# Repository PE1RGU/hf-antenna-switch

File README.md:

# HF Antenna Switch

**A remote antenna switch for an HF amateur radio station: 3 radios, 4 antennas, one Cat6 cable, and the safety rules in hardware.**
**Designed by a radio amateur together with an AI assistant, and documented decision by decision.**

<p align="center"><em>Left: the outdoor unit, lid removed. Right: the shack interface, cover removed. CAD views of the current design, not photos.</em></p>

The relay unit sits outdoors, close to the antennas, in a milled aluminium case.
A small interface box in the shack controls it over one Cat6 cable.
A computer sends the commands over USB.
If anything goes wrong (a cable break, a box fault, a press on the KILL switch), every radio is inhibited and every relay is released, without help from the firmware.

> **Status: design phase.** Schematics, layouts and the case are drawn and checked by scripts. No board is built yet, and nothing here is tested on the bench. The shack interface firmware runs in an emulator on the computer.

## In numbers

| | |
|---|---|
| Radios | 3, each with its own transmit antenna and receive antenna |
| Antennas | 4 per unit; a second unit adds 4 more |
| Frequency range | 1.8 to 54 MHz |
| Power | 100 W, SWR up to 3:1 |
| Relays | 37 × TE RT1, one type everywhere |
| RF board | 6 layers, 50 Ω coplanar lines |
| Link to the shack | One Cat6 cable, four opto-isolated current loops |
| Outdoor case | Milled aluminium tray, 288 × 250 × 66 mm |
| Shack case | Hammond 1455T1601 extrusion, PCB end plates |
| Controllers | ESP32-C3 in the box and in the shack |

## Why this project may interest you

**Safety in hardware, not only in software.**
A receive-only antenna (such as a loop with a preamplifier) never sees transmit power.
No relay switches while RF is present.
The firmware may ask for a state. The hardware decides whether that state is allowed.

**Designed with an AI, in the open.**
This is an experiment in how a person and an AI assistant (Claude, by Anthropic) design hardware together.
I set the goals and took the decisions. The AI did much of the research, the calculations and the scripts.
The [design log](design-log.md) records every decision, who took it, and why. Rejected options stay in it too.
See [docs/how-this-was-made.md](docs/how-this-was-made.md) for the method and its limits.

**Everything comes from scripts.**
Schematics, footprints, board placement, routing, end plates, the 3D fit checks and these renders are all generated by Python scripts.
A change is repeatable, and two revisions can be compared.
The logic is checked with truth tables against the real netlists.
[tools/README.md](tools/README.md) lists every script and how to run it.

## What it does

- Connects each of 3 radios to a transmit antenna and, separately, to a receive antenna.
- Keeps receive-only antennas away from transmit power.
- Changes relays only when no RF is present (TX inhibit and handshake per radio).
- Stops all transmission and releases all relays on any fault, cable break or KILL switch.
- Grounds antennas that are not in use, through a static bleed.
- Feeds an active receive antenna through a switched bias-T.
- Is controlled from a computer over USB through the shack interface.

## System overview

```mermaid
flowchart LR
  subgraph SHACK["Shack"]
    PC["Computer"]
    SI["Shack interface<br/>SAFE latch, TX permits,<br/>radio ports R1 to R3"]
    R1["R1 FT-710"]
    R2["R2"]
    R3["R3"]
  end
  subgraph BOX["Outdoor unit, milled aluminium case"]
    CB["Controller board<br/>ESP32-C3, safety gate, watchdog"]
    RF["RF board<br/>3 radios x 4 antennas<br/>37 x TE RT1 relays"]
  end
  subgraph ANT["Antennas"]
    A1["A1 G5RV"]
    A2["A2 RX loop"]
    A34["A3, A4 spare"]
  end
  U2["Unit 2, optional<br/>+4 antennas"]
  PC -- USB --> SI
  SI == "Cat6: 4 opto current loops" ==> CB
  CB -- I2C --> RF
  R1 -- coax --> RF
  R2 -- coax --> RF
  R3 -- coax --> RF
  R1 -.- SI
  R2 -.- SI
  R3 -.- SI
  RF --> A1
  RF --> A2
  RF --> A34
  RF -. "EXP: SMA + ribbon" .-> U2
```

The dotted lines from the radios are the TUNER and LINEAR jacks (TX inhibit, PTT sense).
More detail, and the reason for each choice, is in [docs/architecture.md](docs/architecture.md).

## The outdoor unit

The RF board carries the relay matrix: per radio a changeover relay, a transmit row and a receive row; per antenna a ground relay, a static bleed, an RF detector and an optional bias-T.
The controller board sits on standoffs above it.

<p align="center"><em>Controller board (KiCad render). Left: the Cat6 link with the opto current loops and a 3 mm isolation gap. Right: the ESP32-C3 DevKit. The NOR gate on the silkscreen is the relay enable: RLY_EN = NOR(KILL, MCU_EN_N, FAULT).</em></p>

## The shack interface

The shack interface powers the four current loops, holds the SAFE latch and the transmit permits, and connects to the three radios.
At the front: a 2 inch colour display, the SAFE and LATCHED LEDs, RESET and the KILL switch.
At the rear: 13.8 V DC, Cat6 to the outdoor unit, USB and the three radio ports.

<p align="center"><em>Front and rear of the shack interface (SolidCraft views).</em></p>

## Safety chain

The SAFE loop is one series current loop from the shack to the box and back.
Any break stops the current: KILL switch, cable cut, box fault, or loss of power.
All radios are then inhibited and all relays released, in hardware, without help from the firmware.

Radios R2 and R3 transmit only after a handshake with the box: request, state check, relay set, read-back, permit.

All logic, timing and flow diagrams:

| Diagram | Content |
|---|---|
| [L1](hardware/docs/diagrams/L1_safe_loop.svg) | SAFE loop |
| [L2](hardware/docs/diagrams/L2_box_safety_gate.svg) | Box safety gate |
| [L3](hardware/docs/diagrams/L3_shack_latch_port.svg) | Shack latch and radio port |
| [T1](hardware/docs/diagrams/T1_box_startup.svg) | Box start-up timing |
| [T2](hardware/docs/diagrams/T2_safe_stop.svg) | SAFE stop timing |
| [T3a](hardware/docs/diagrams/T3a_tx_start.svg), [T3b](hardware/docs/diagrams/T3b_tx_end.svg) | TX start and TX end timing |
| [T4](hardware/docs/diagrams/T4_ptt_r1.svg) | R1 PTT loop timing |
| [F1](hardware/docs/diagrams/F1_box_firmware.svg) | Box firmware flow |
| [F2](hardware/docs/diagrams/F2_tx_handshake.svg) | TX handshake for R2 and R3 |

## Firmware and emulator

The firmware is written in Rust and runs on an ESP32-C3 in the box and in the shack.
No board exists yet, so the firmware is developed in an emulator.
The emulator runs the same firmware logic that goes into the ESP32-C3, against models of the parts on the board: the I/O expander, the supervisors and latches, the SAFE loop, the radio ports, the data link to the box and the display.

<p align="center"><em>The emulated shack interface in a terminal. Left: pixel view, the 2 inch display exactly as the firmware draws it. Right: text view, for terminals without images. R1 transmits on A1 and receives on the loop A2; R2 uses A3.</em></p>

In the emulator you can:

- see the shack display as the firmware draws it (page B: radios, antennas and their routes; page C: one card per radio; the Safe stop screen with its cause and the steps to recover),
- press RESET and KILL, cut the cable, switch the supply, and let a radio transmit, with function keys,
- type the same commands that a station program sends over USB, or connect a program over TCP,
- stop it and start it again: the routes, names and page come back, as on the real unit; a transmission never does.

It runs in a terminal on macOS, Linux and Windows:

```bash
cd firmware
```

```bash
cargo run --release -p sim-shack
```

[firmware/README.md](firmware/README.md) explains how the emulator works, every key and command, and a first session step by step.
To read or change the code, start with the [firmware guide](firmware/docs/guide.md), written for hobby programmers.

## Where it stands

| Part | State |
|---|---|
| Requirements and architecture | Requirements in draft, architecture rev C |
| Schematics, all boards | Generated, ERC clean, logic checked by script |
| RF board layout | Placed and routed, DRC clean |
| Controller board layout | Placed and routed, DRC clean |
| Shack interface layout | Placed and routed, DRC clean; end plates drawn |
| Cases | Outdoor tray and shack end plates drawn; 3D fit checked |
| Firmware, shack interface | Runs in the emulator: permits, handshake, host protocol, display, stored settings; tested against the hardware logic |
| Firmware, box controller | Not started; a scripted box stands in for it in the emulator |
| Bench tests | Not started; see [docs/test/test-spec.md](docs/test/test-spec.md) |

The [CHANGELOG](CHANGELOG.md) has the details per revision.

## Documents

| Document | Content |
|---|---|
| [docs/requirements.md](docs/requirements.md) | What we build and what is important |
| [docs/architecture.md](docs/architecture.md) | System blocks, interfaces, main decisions |
| [docs/design/](docs/design/) | Detailed design, one document per board |
| [docs/test/test-spec.md](docs/test/test-spec.md) | How each requirement is tested |
| [design-log.md](design-log.md) | Every decision, assumption, calculation, standard and measurement, with its reason |
| [CHANGELOG.md](CHANGELOG.md) | Changes per revision |

## Repository layout

```
docs/                       requirements, architecture, design, test, images
hardware/unit/              outdoor unit: RF board, controller board, case, verification scripts
hardware/shack-interface/   shack interface board, end plates, case fit and renders
hardware/docs/diagrams/     logic, timing and flow diagrams
firmware/                   Rust firmware and the emulator (see firmware/README.md)
tools/README.md             where each generator and verification script is, and how to run it
Datasheets/                 datasheet register (the PDFs are not in the repository)
archive/                    earlier revisions (card cage and backplane, rev A/B)
```

## Tools

- KiCad 10, with the board layouts generated by Python scripts
- Rust for the firmware and the emulator (esp-hal, embedded-graphics, ratatui)
- Python 3 for the generators, the router and the verification scripts
- cadquery and SolidCraft for the cases, the 3D fit checks and the renders
- JLCPCB for the PCBs

## Licence

- Hardware design files and documentation: CERN Open Hardware Licence v2, Strongly Reciprocal (CERN-OHL-S-2.0). See [LICENSE](LICENSE).
- Python scripts (generators, verification) and the firmware (Rust): MIT. See [LICENSE-MIT](LICENSE-MIT).
- The display fonts compiled into the firmware are M+ FONTS (through the `mplusfonts` crate), under the SIL Open Font License 1.1.
- Vendor 3D models and libraries (SnapEDA, SamacSys, Ultra Librarian, Amass, Amphenol) are not in the repository. See [hardware/THIRD-PARTY.md](hardware/THIRD-PARTY.md) for where to get them.

Source Location (required by CERN-OHL-S): https://github.com/PE1RGU/hf-antenna-switch

73 de PE1RGU

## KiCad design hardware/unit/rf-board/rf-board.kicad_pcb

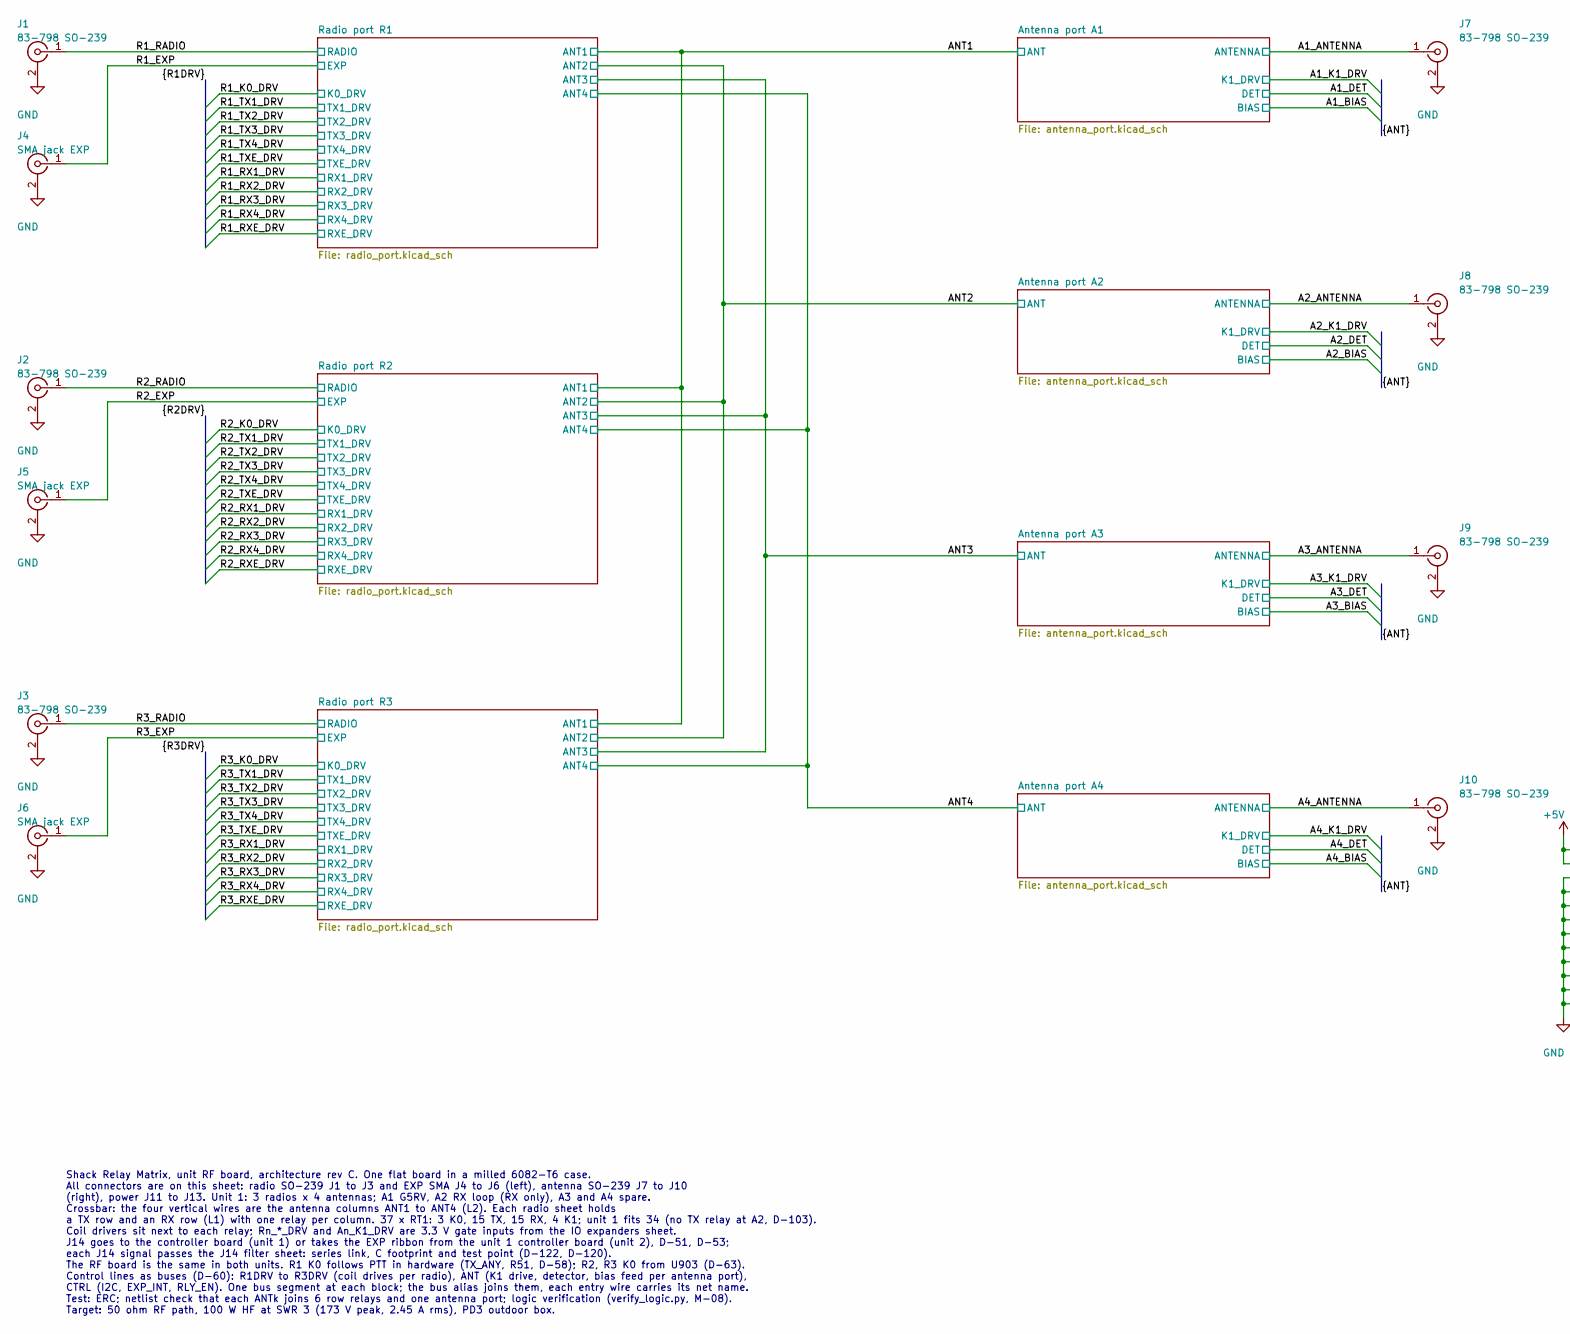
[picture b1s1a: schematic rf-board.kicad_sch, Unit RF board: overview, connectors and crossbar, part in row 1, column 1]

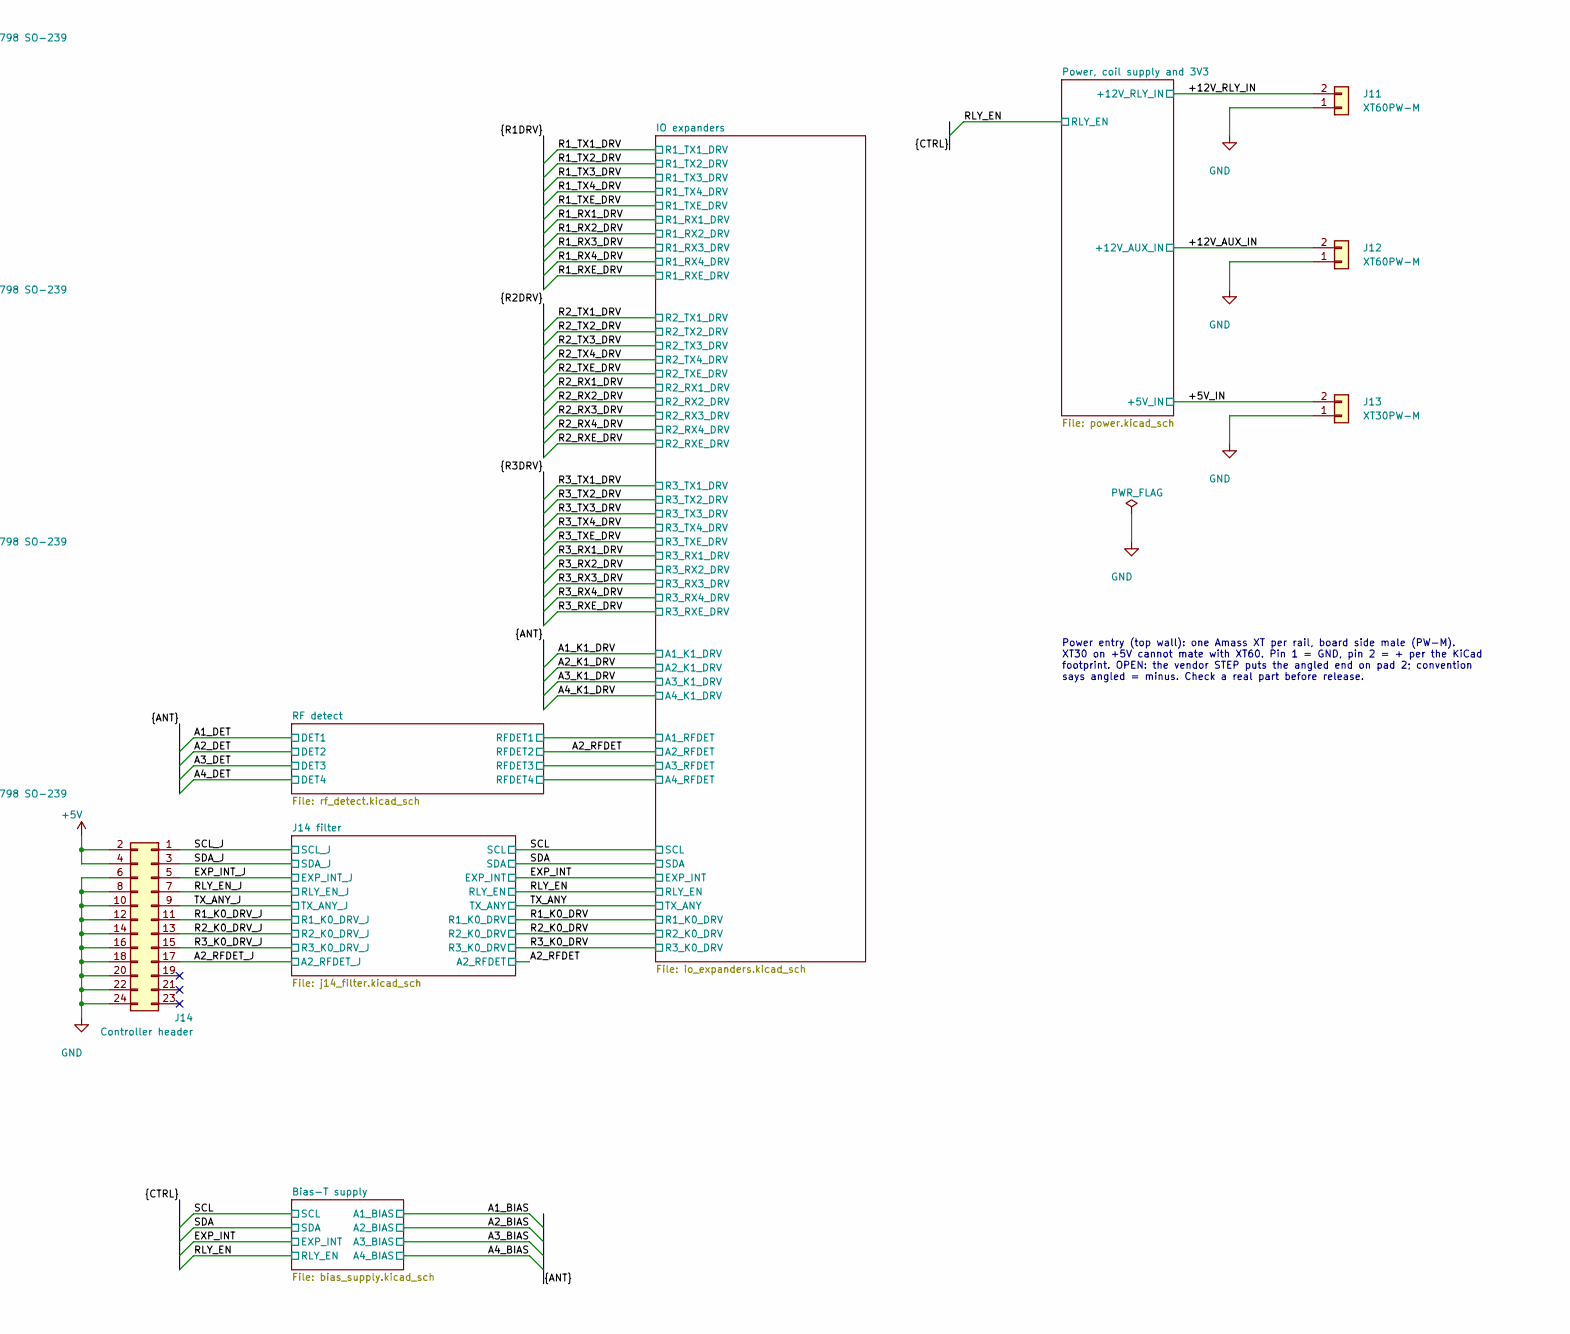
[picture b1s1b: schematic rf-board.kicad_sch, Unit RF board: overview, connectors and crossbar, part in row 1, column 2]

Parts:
J1, J2, J3, J7, J8, J9: 83-798 SO-239; SO239_83-798_StrapPad_BossRight; MPN 83-1R
J4, J5, J6: SMA jack EXP; SMA_901-9215_StrapPad; MPN 901-9215
J10: 83-798 SO-239; SO239_83-798_StrapPad_BossLeft; MPN 83-1R
J11, J12: XT60PW-M; AMASS_XT60PW-M_1x02_P7.20mm_Horizontal; MPN XT60PW-M
J13: XT30PW-M; AMASS_XT30PW-M_1x02_P2.50mm_Horizontal; MPN XT30PW-M
J14: Controller header; PinHeader_2x12_P2.54mm_Vertical; MPN TSW-112-07-L-D

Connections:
+5V: J14.2, J14.4; also elsewhere on the board
/+5V_IN: J13.2; also elsewhere on the board
/+12V_AUX_IN: J12.2; also elsewhere on the board
/+12V_RLY_IN: J11.2; also elsewhere on the board
/A1_ANTENNA: J7.1 (In); also elsewhere on the board
/A2_ANTENNA: J8.1 (In); also elsewhere on the board
/A2_RFDET_J: J14.17; also elsewhere on the board
/A3_ANTENNA: J9.1 (In); also elsewhere on the board
/A4_ANTENNA: J10.1 (In); also elsewhere on the board
/EXP_INT_J: J14.5; also elsewhere on the board
/R1_EXP: J4.1 (In); also elsewhere on the board
/R1_K0_DRV_J: J14.11; also elsewhere on the board
/R1_RADIO: J1.1 (In); also elsewhere on the board
/R2_EXP: J5.1 (In); also elsewhere on the board
/R2_K0_DRV_J: J14.13; also elsewhere on the board
/R2_RADIO: J2.1 (In); also elsewhere on the board
/R3_EXP: J6.1 (In); also elsewhere on the board
/R3_K0_DRV_J: J14.15; also elsewhere on the board
/R3_RADIO: J3.1 (In); also elsewhere on the board
/RLY_EN_J: J14.7; also elsewhere on the board
/SCL_J: J14.1; also elsewhere on the board
/SDA_J: J14.3; also elsewhere on the board
/TX_ANY_J: J14.9; also elsewhere on the board
GND: J1.2 (Ext), J2.2 (Ext), J3.2 (Ext), J4.2 (Ext), J5.2 (Ext), J6.2 (Ext), J7.2 (Ext), J8.2 (Ext), J9.2 (Ext), J10.2 (Ext), J11.1, J12.1, J13.1, J14.6, J14.8, J14.10, J14.12, J14.14, J14.16, J14.18, J14.20, J14.22, J14.24; also elsewhere on the board

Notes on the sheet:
Power entry (top wall): one Amass XT per rail, board side male (PW-M). XT30 on +5V cannot mate with XT60. Pin 1 = GND, pin 2 = + per the KiCad footprint. OPEN: the vendor STEP puts the angled end on pad 2; convention says angled = minus. Check a real part before release.
Shack Relay Matrix, unit RF board, architecture rev C. One flat board in a milled 6082-T6 case. All connectors are on this sheet: radio SO-239 J1 to J3 and EXP SMA J4 to J6 (left), antenna SO-239 J7 to J10 (right), power J11 to J13. Unit 1: 3 radios x 4 antennas; A1 G5RV, A2 RX loop (RX only), A3 a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

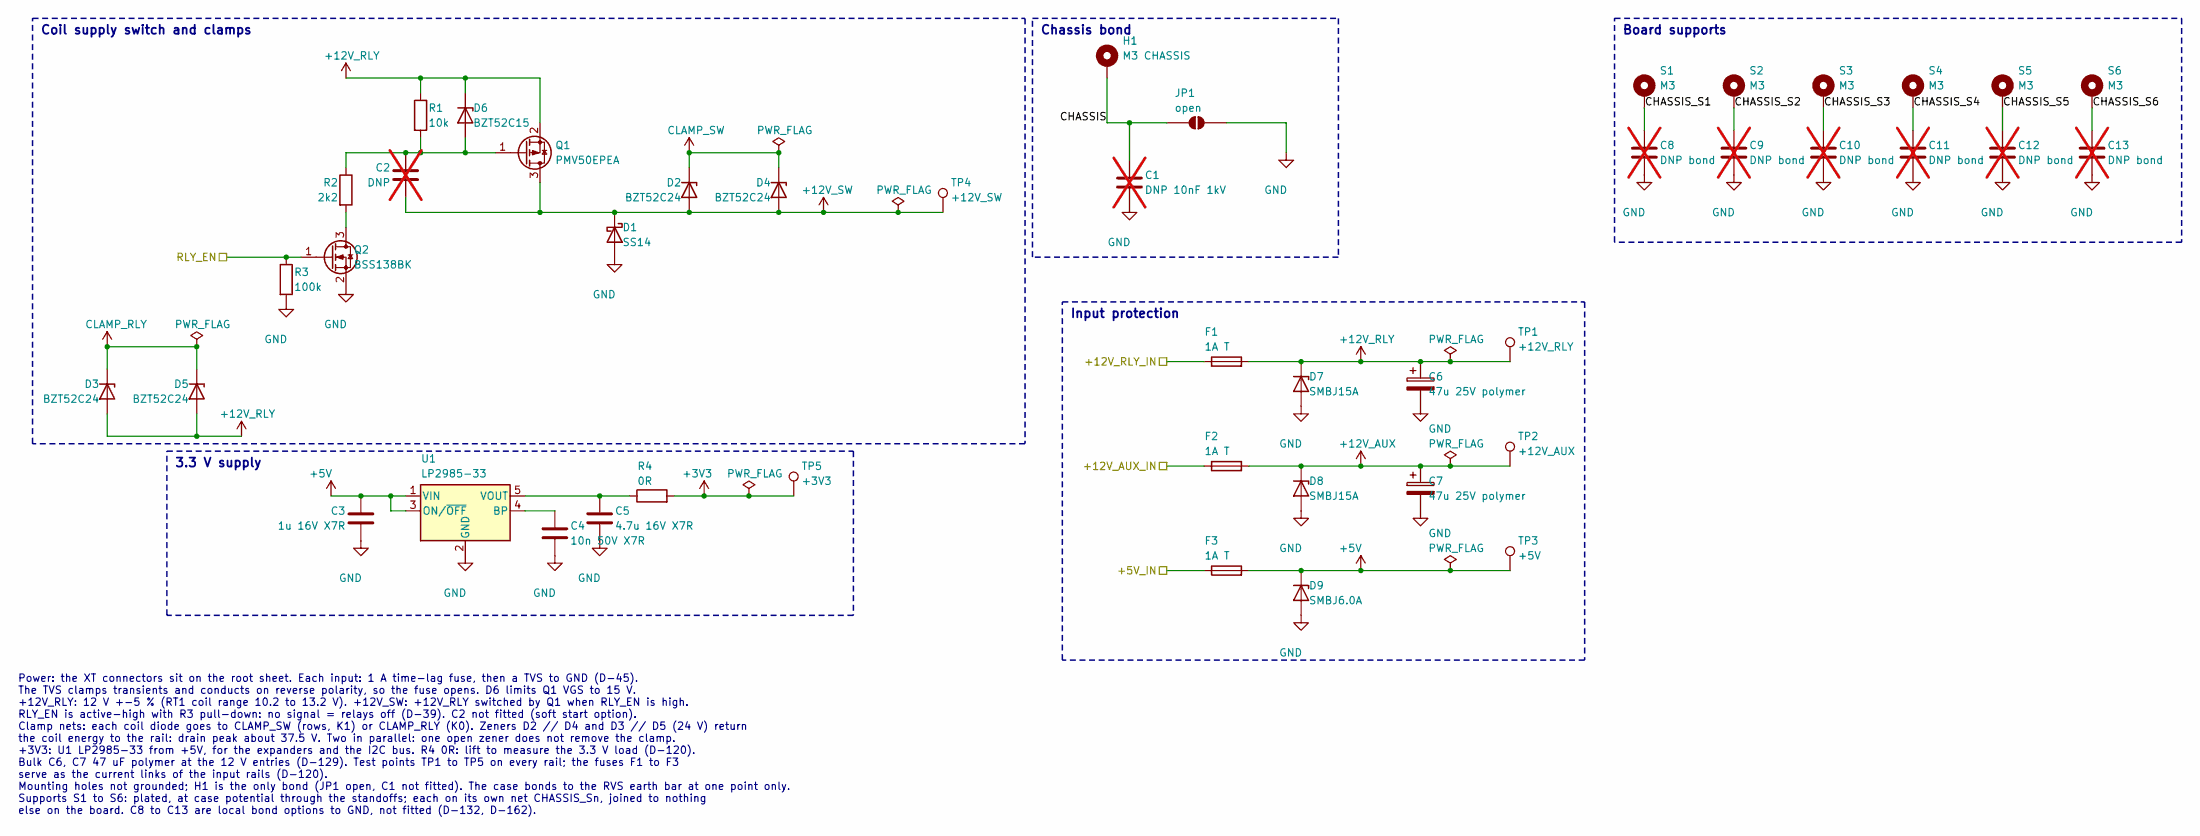
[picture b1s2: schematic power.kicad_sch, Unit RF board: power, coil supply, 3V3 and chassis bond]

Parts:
C1: DNP 10nF 1kV; C_1206_3216Metric_Pad1.33x1.80mm_HandSolder; not fitted
C2: DNP; C_0603_1608Metric_Pad1.08x0.95mm_HandSolder; not fitted
C3: 1u 16V X7R; C_0603_1608Metric_Pad1.08x0.95mm_HandSolder
C4: 10n 50V X7R; C_0603_1608Metric_Pad1.08x0.95mm_HandSolder
C5: 4.7u 16V X7R; C_0805_2012Metric_Pad1.18x1.45mm_HandSolder
C6, C7: 47u 25V polymer; CP_Elec_6.3x7.7
C8, C9, C10, C11, C12, C13: DNP bond; C_1206_3216Metric_Pad1.33x1.80mm_HandSolder; not fitted
D1: SS14; D_SMA; MPN SS14
D2, D3, D4, D5: BZT52C24; D_SOD-123; MPN BZT52H-C24,115
D6: BZT52C15; D_SOD-123; MPN BZT52C15
D7, D8: SMBJ15A; D_SMB; MPN SMBJ15A
D9: SMBJ6.0A; D_SMB; MPN SMBJ6.0A
F1, F2, F3: 1A T; Fuse_1206_3216Metric_Pad1.42x1.75mm_HandSolder; MPN 0468001.NR
H1: M3 CHASSIS; MountingHole_3.2mm_M3_Pad
JP1: open; SolderJumper-2_P1.3mm_Open_RoundedPad1.0x1.5mm
Q1: PMV50EPEA; SOT-23; MPN PMV50EPEA
Q2: BSS138BK; SOT-23; MPN BSS138BK,215
R1: 10k; R_0603_1608Metric_Pad0.98x0.95mm_HandSolder
R2: 2k2; R_0603_1608Metric_Pad0.98x0.95mm_HandSolder
R3: 100k; R_0603_1608Metric_Pad0.98x0.95mm_HandSolder
R4: 0R; R_1206_3216Metric_Pad1.30x1.75mm_HandSolder
S1, S2, S3, S4, S5, S6: M3; MountingHole_3.2mm_M3_Pad
TP1: +12V_RLY; TestPoint_Pad_D1.5mm
TP2: +12V_AUX; TestPoint_Pad_D1.5mm
TP3: +5V; TestPoint_Pad_D1.5mm
TP4: +12V_SW; TestPoint_Pad_D1.5mm
TP5: +3V3; TestPoint_Pad_D1.5mm
U1: LP2985-33; SOT-23-5; MPN LP2985-33DBVR

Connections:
+3V3: R4.2, TP5.1; also elsewhere on the board
+5V: C3.1, D9.1 (K), F3.2, TP3.1, U1.1 (VIN), U1.3 (ON/~OFF); also elsewhere on the board
+12V_AUX: C7.1, D8.1 (K), F2.2, TP2.1; also elsewhere on the board
+12V_RLY: C6.1, D3.2 (A), D5.2 (A), D6.1 (K), D7.1 (K), F1.2, Q1.2 (S), R1.1, TP1.1; also elsewhere on the board
+12V_SW: C2.2, D1.1 (K), D2.2 (A), D4.2 (A), Q1.3 (D), TP4.1; also elsewhere on the board
/+5V_IN: F3.1; also elsewhere on the board
/+12V_AUX_IN: F2.1; also elsewhere on the board
/+12V_RLY_IN: F1.1; also elsewhere on the board
/Power, coil supply and 3V3/CHASSIS: C1.1, H1.1, JP1.1 (A)
/Power, coil supply and 3V3/CHASSIS_S1: C8.1, S1.1
/Power, coil supply and 3V3/CHASSIS_S2: C9.1, S2.1
/Power, coil supply and 3V3/CHASSIS_S3: C10.1, S3.1
/Power, coil supply and 3V3/CHASSIS_S4: C11.1, S4.1
/Power, coil supply and 3V3/CHASSIS_S5: C12.1, S5.1
/Power, coil supply and 3V3/CHASSIS_S6: C13.1, S6.1
/RLY_EN: Q2.1 (G), R3.1; also elsewhere on the board
CLAMP_RLY: D3.1 (K), D5.1 (K); also elsewhere on the board
CLAMP_SW: D2.1 (K), D4.1 (K); also elsewhere on the board
GND: C1.2, C3.2, C4.2, C5.2, C6.2, C7.2, C8.2, C9.2, C10.2, C11.2, C12.2, C13.2, D1.2 (A), D7.2 (A), D8.2 (A), D9.2 (A), JP1.2 (B), Q2.2 (S), R3.2, U1.2 (GND); also elsewhere on the board
unnamed: C2.1, D6.2 (A), Q1.1 (G), R1.2, R2.1
unnamed: Q2.3 (D), R2.2
unnamed: C4.1, U1.4 (BP)
unnamed: C5.1, R4.1, U1.5 (VOUT)

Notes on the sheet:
Power: the XT connectors sit on the root sheet. Each input: 1 A time-lag fuse, then a TVS to GND (D-45). The TVS clamps transients and conducts on reverse polarity, so the fuse opens. D6 limits Q1 VGS to 15 V. +12V_RLY: 12 V +-5 % (RT1 coil range 10.2 to 13.2 V). +12V_SW: +12V_RLY switched by Q1 wh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
Coil supply switch and clamps
Chassis bond
Input protection
3.3 V supply
Board supports

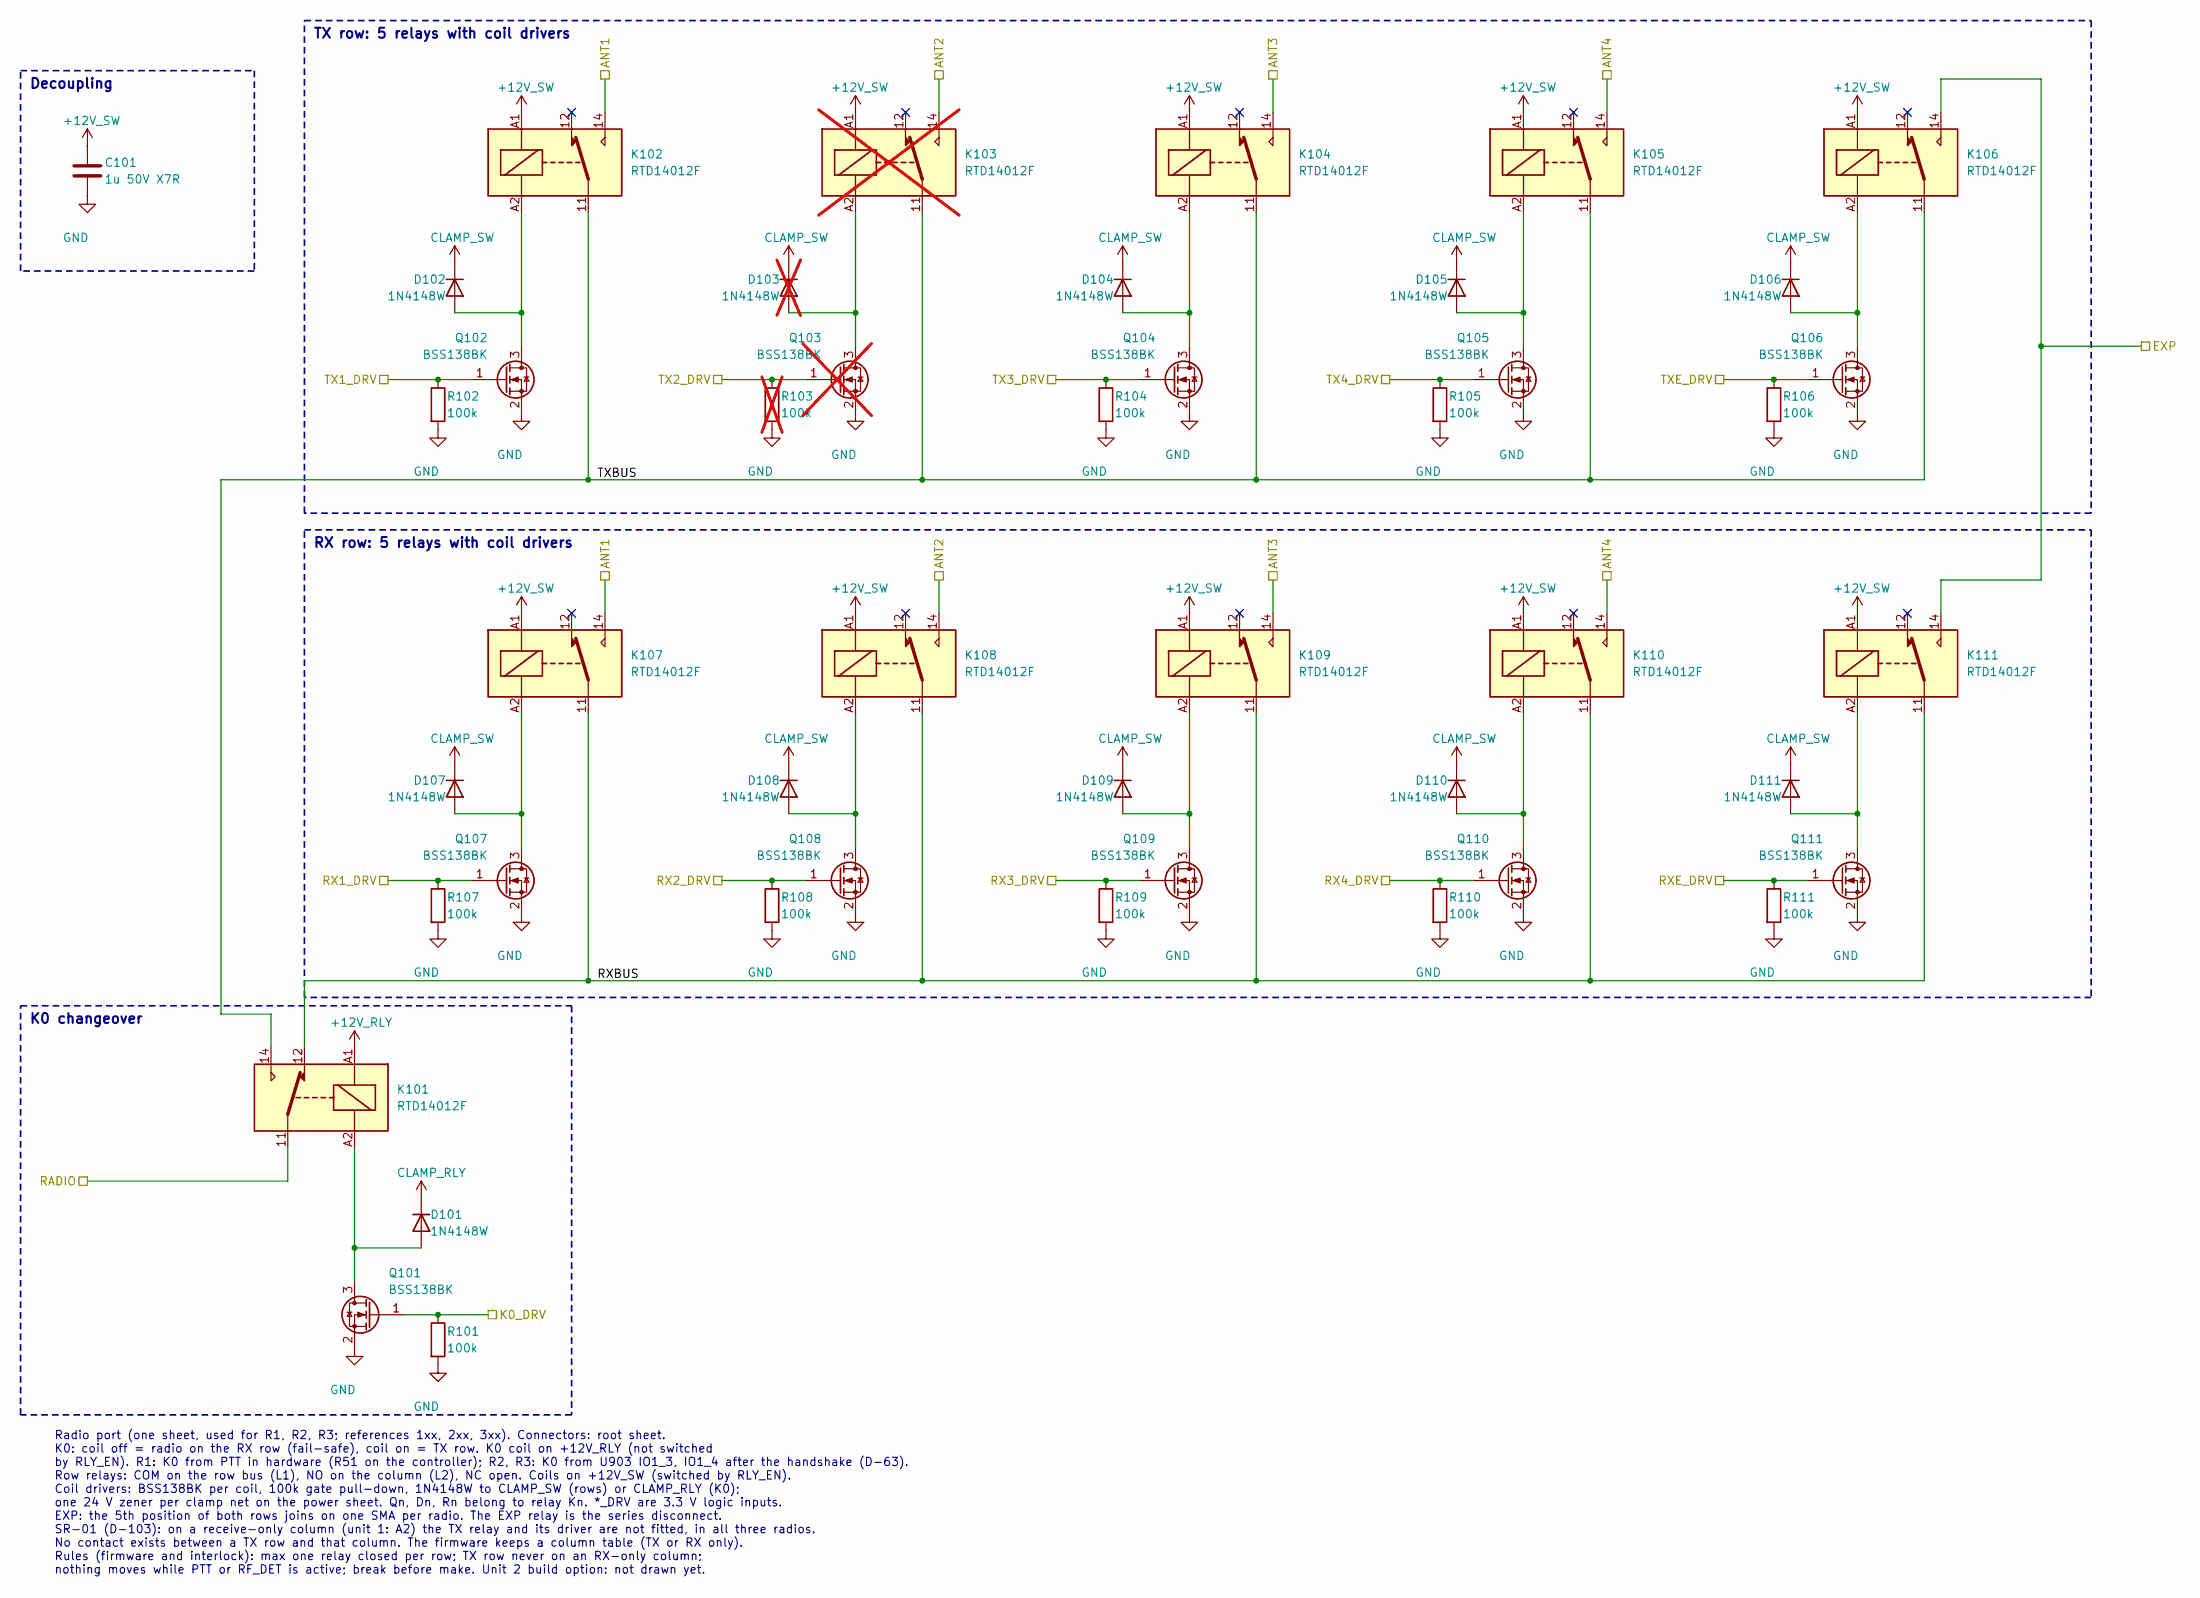
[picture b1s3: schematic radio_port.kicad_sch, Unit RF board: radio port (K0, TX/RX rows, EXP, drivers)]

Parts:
C101: 1u 50V X7R; C_0805_2012Metric_Pad1.18x1.45mm_HandSolder
D101, D102, D104, D105, D106, D107, D108, D109, D110, D111: 1N4148W; D_SOD-123; MPN 1N4148W
D103: 1N4148W; D_SOD-123; MPN 1N4148W; not fitted
K101, K102, K104, K105, K106, K107, K108, K109, K110, K111: RTD14012F; Relay_SPDT_Schrack-RT1-16A-FormC_RM5mm; MPN RTD14012F
K103: RTD14012F; Relay_SPDT_Schrack-RT1-16A-FormC_RM5mm; MPN RTD14012F; not fitted
Q101, Q102, Q104, Q105, Q106, Q107, Q108, Q109, Q110, Q111: BSS138BK; SOT-23; MPN BSS138BK,215
Q103: BSS138BK; SOT-23; MPN BSS138BK,215; not fitted
R101, R102, R104, R105, R106, R107, R108, R109, R110, R111: 100k; R_0603_1608Metric_Pad0.98x0.95mm_HandSolder
R103: 100k; R_0603_1608Metric_Pad0.98x0.95mm_HandSolder; not fitted

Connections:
+12V_RLY: K101.A1; also elsewhere on the board
+12V_SW: C101.1, K102.A1, K103.A1, K104.A1, K105.A1, K106.A1, K107.A1, K108.A1, K109.A1, K110.A1, K111.A1; also elsewhere on the board
/ANT1: K102.14, K107.14; also elsewhere on the board
/ANT2: K103.14, K108.14; also elsewhere on the board
/ANT3: K104.14, K109.14; also elsewhere on the board
/ANT4: K105.14, K110.14; also elsewhere on the board
/R1_EXP: K106.14, K111.14; also elsewhere on the board
/R1_K0_DRV: Q101.1 (G), R101.1; also elsewhere on the board
/R1_RADIO: K101.11; also elsewhere on the board
/R1_RX1_DRV: Q107.1 (G), R107.1; also elsewhere on the board
/R1_RX2_DRV: Q108.1 (G), R108.1; also elsewhere on the board
/R1_RX3_DRV: Q109.1 (G), R109.1; also elsewhere on the board
/R1_RX4_DRV: Q110.1 (G), R110.1; also elsewhere on the board
/R1_RXE_DRV: Q111.1 (G), R111.1; also elsewhere on the board
/R1_TX1_DRV: Q102.1 (G), R102.1; also elsewhere on the board
/R1_TX2_DRV: Q103.1 (G), R103.1; also elsewhere on the board
/R1_TX3_DRV: Q104.1 (G), R104.1; also elsewhere on the board
/R1_TX4_DRV: Q105.1 (G), R105.1; also elsewhere on the board
/R1_TXE_DRV: Q106.1 (G), R106.1; also elsewhere on the board
/Radio port R1/RXBUS: K101.12, K107.11, K108.11, K109.11, K110.11, K111.11
/Radio port R1/TXBUS: K101.14, K102.11, K103.11, K104.11, K105.11, K106.11
CLAMP_RLY: D101.1 (K); also elsewhere on the board
CLAMP_SW: D102.1 (K), D103.1 (K), D104.1 (K), D105.1 (K), D106.1 (K), D107.1 (K), D108.1 (K), D109.1 (K), D110.1 (K), D111.1 (K); also elsewhere on the board
GND: C101.2, Q101.2 (S), Q102.2 (S), Q103.2 (S), Q104.2 (S), Q105.2 (S), Q106.2 (S), Q107.2 (S), Q108.2 (S), Q109.2 (S), Q110.2 (S), Q111.2 (S), R101.2, R102.2, R103.2, R104.2, R105.2, R106.2, R107.2, R108.2, R109.2, R110.2, R111.2; also elsewhere on the board
unnamed: D101.2 (A), K101.A2, Q101.3 (D)
unnamed: D102.2 (A), K102.A2, Q102.3 (D)
unnamed: D103.2 (A), K103.A2, Q103.3 (D)
unnamed: D104.2 (A), K104.A2, Q104.3 (D)
unnamed: D105.2 (A), K105.A2, Q105.3 (D)
unnamed: D106.2 (A), K106.A2, Q106.3 (D)
unnamed: D107.2 (A), K107.A2, Q107.3 (D)
unnamed: D108.2 (A), K108.A2, Q108.3 (D)
unnamed: D109.2 (A), K109.A2, Q109.3 (D)
unnamed: D110.2 (A), K110.A2, Q110.3 (D)
unnamed: D111.2 (A), K111.A2, Q111.3 (D)

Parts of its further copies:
C201, C301: 1u 50V X7R; C_0805_2012Metric_Pad1.18x1.45mm_HandSolder
D201, D202, D204, D205, D206, D207, D208, D209, D210, D211, D301, D302, D304, D305, D306, D307, D308, D309, D310, D311: 1N4148W; D_SOD-123; MPN 1N4148W
D203, D303: 1N4148W; D_SOD-123; MPN 1N4148W; not fitted
K201, K202, K204, K205, K206, K207, K208, K209, K210, K211, K301, K302, K304, K305, K306, K307, K308, K309, K310, K311: RTD14012F; Relay_SPDT_Schrack-RT1-16A-FormC_RM5mm; MPN RTD14012F
K203, K303: RTD14012F; Relay_SPDT_Schrack-RT1-16A-FormC_RM5mm; MPN RTD14012F; not fitted
Q201, Q202, Q204, Q205, Q206, Q207, Q208, Q209, Q210, Q211, Q301, Q302, Q304, Q305, Q306, Q307, Q308, Q309, Q310, Q311: BSS138BK; SOT-23; MPN BSS138BK,215
Q203, Q303: BSS138BK; SOT-23; MPN BSS138BK,215; not fitted
R201, R202, R204, R205, R206, R207, R208, R209, R210, R211, R301, R302, R304, R305, R306, R307, R308, R309, R310, R311: 100k; R_0603_1608Metric_Pad0.98x0.95mm_HandSolder
R203, R303: 100k; R_0603_1608Metric_Pad0.98x0.95mm_HandSolder; not fitted

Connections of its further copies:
+12V_RLY: K201.A1, K301.A1; also elsewhere on the board
+12V_SW: C201.1, C301.1, K202.A1, K203.A1, K204.A1, K205.A1, K206.A1, K207.A1, K208.A1, K209.A1, K210.A1, K211.A1, K302.A1, K303.A1, K304.A1, K305.A1, K306.A1, K307.A1, K308.A1, K309.A1, K310.A1, K311.A1; also elsewhere on the board
/ANT1: K202.14, K207.14, K302.14, K307.14; also elsewhere on the board
/ANT2: K203.14, K208.14, K303.14, K308.14; also elsewhere on the board
/ANT3: K204.14, K209.14, K304.14, K309.14; also elsewhere on the board
/ANT4: K205.14, K210.14, K305.14, K310.14; also elsewhere on the board
/R2_EXP: K206.14, K211.14; also elsewhere on the board
/R2_K0_DRV: Q201.1 (G), R201.1; also elsewhere on the board
/R2_RADIO: K201.11; also elsewhere on the board
/R2_RX1_DRV: Q207.1 (G), R207.1; also elsewhere on the board
/R2_RX2_DRV: Q208.1 (G), R208.1; also elsewhere on the board
/R2_RX3_DRV: Q209.1 (G), R209.1; also elsewhere on the board
/R2_RX4_DRV: Q210.1 (G), R210.1; also elsewhere on the board
/R2_RXE_DRV: Q211.1 (G), R211.1; also elsewhere on the board
/R2_TX1_DRV: Q202.1 (G), R202.1; also elsewhere on the board
/R2_TX2_DRV: Q203.1 (G), R203.1; also elsewhere on the board
/R2_TX3_DRV: Q204.1 (G), R204.1; also elsewhere on the board
/R2_TX4_DRV: Q205.1 (G), R205.1; also elsewhere on the board
/R2_TXE_DRV: Q206.1 (G), R206.1; also elsewhere on the board
/R3_EXP: K306.14, K311.14; also elsewhere on the board
/R3_K0_DRV: Q301.1 (G), R301.1; also elsewhere on the board
/R3_RADIO: K301.11; also elsewhere on the board
/R3_RX1_DRV: Q307.1 (G), R307.1; also elsewhere on the board
/R3_RX2_DRV: Q308.1 (G), R308.1; also elsewhere on the board
/R3_RX3_DRV: Q309.1 (G), R309.1; also elsewhere on the board
/R3_RX4_DRV: Q310.1 (G), R310.1; also elsewhere on the board
/R3_RXE_DRV: Q311.1 (G), R311.1; also elsewhere on the board
/R3_TX1_DRV: Q302.1 (G), R302.1; also elsewhere on the board
/R3_TX2_DRV: Q303.1 (G), R303.1; also elsewhere on the board
/R3_TX3_DRV: Q304.1 (G), R304.1; also elsewhere on the board
/R3_TX4_DRV: Q305.1 (G), R305.1; also elsewhere on the board
/R3_TXE_DRV: Q306.1 (G), R306.1; also elsewhere on the board
/Radio port R2/RXBUS: K201.12, K207.11, K208.11, K209.11, K210.11, K211.11
/Radio port R2/TXBUS: K201.14, K202.11, K203.11, K204.11, K205.11, K206.11
/Radio port R3/RXBUS: K301.12, K307.11, K308.11, K309.11, K310.11, K311.11
/Radio port R3/TXBUS: K301.14, K302.11, K303.11, K304.11, K305.11, K306.11
CLAMP_RLY: D201.1 (K), D301.1 (K); also elsewhere on the board
CLAMP_SW: D202.1 (K), D203.1 (K), D204.1 (K), D205.1 (K), D206.1 (K), D207.1 (K), D208.1 (K), D209.1 (K), D210.1 (K), D211.1 (K), D302.1 (K), D303.1 (K), D304.1 (K), D305.1 (K), D306.1 (K), D307.1 (K), D308.1 (K), D309.1 (K), D310.1 (K), D311.1 (K); also elsewhere on the board
GND: C201.2, C301.2, Q201.2 (S), Q202.2 (S), Q203.2 (S), Q204.2 (S), Q205.2 (S), Q206.2 (S), Q207.2 (S), Q208.2 (S), Q209.2 (S), Q210.2 (S), Q211.2 (S), Q301.2 (S), Q302.2 (S), Q303.2 (S), Q304.2 (S), Q305.2 (S), Q306.2 (S), Q307.2 (S), Q308.2 (S), Q309.2 (S), Q310.2 (S), Q311.2 (S), R201.2, R202.2, R203.2, R204.2, R205.2, R206.2, R207.2, R208.2, R209.2, R210.2, R211.2, R301.2, R302.2, R303.2, R304.2, R305.2, R306.2, R307.2, R308.2, R309.2, R310.2, R311.2; also elsewhere on the board
unnamed: D201.2 (A), K201.A2, Q201.3 (D)
unnamed: D202.2 (A), K202.A2, Q202.3 (D)
unnamed: D203.2 (A), K203.A2, Q203.3 (D)
unnamed: D204.2 (A), K204.A2, Q204.3 (D)
unnamed: D205.2 (A), K205.A2, Q205.3 (D)
unnamed: D206.2 (A), K206.A2, Q206.3 (D)
unnamed: D207.2 (A), K207.A2, Q207.3 (D)
unnamed: D208.2 (A), K208.A2, Q208.3 (D)
unnamed: D209.2 (A), K209.A2, Q209.3 (D)
unnamed: D210.2 (A), K210.A2, Q210.3 (D)
unnamed: D211.2 (A), K211.A2, Q211.3 (D)
unnamed: D301.2 (A), K301.A2, Q301.3 (D)
unnamed: D302.2 (A), K302.A2, Q302.3 (D)
unnamed: D303.2 (A), K303.A2, Q303.3 (D)
unnamed: D304.2 (A), K304.A2, Q304.3 (D)
unnamed: D305.2 (A), K305.A2, Q305.3 (D)
unnamed: D306.2 (A), K306.A2, Q306.3 (D)
unnamed: D307.2 (A), K307.A2, Q307.3 (D)
unnamed: D308.2 (A), K308.A2, Q308.3 (D)
unnamed: D309.2 (A), K309.A2, Q309.3 (D)
unnamed: D310.2 (A), K310.A2, Q310.3 (D)
unnamed: D311.2 (A), K311.A2, Q311.3 (D)

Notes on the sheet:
Radio port (one sheet, used for R1, R2, R3; references 1xx, 2xx, 3xx). Connectors: root sheet. K0: coil off = radio on the RX row (fail-safe), coil on = TX row. K0 coil on +12V_RLY (not switched by RLY_EN). R1: K0 from PTT in hardware (R51 on the controller); R2, R3: K0 from U903 IO1_3, IO1_4 after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
TX row: 5 relays with coil drivers
RX row: 5 relays with coil drivers
K0 changeover
Decoupling

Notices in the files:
README.md:
Hardware: CERN-OHL-S-2.0
